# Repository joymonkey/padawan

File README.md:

# padawan
Padawan Pan-Galactic Sketch

Based on DanF's PADAWAN sketch for PS2 controllers, this sketch is intended to allow the use of PS2, PS3, PS4 or XBox 360 controllers depending on compile options set at the start of the sketch.

Tested with an Arduino Mega ADK, Padawan Shield, AZIO Class 1 Bluetooth USB Dongle, PS4 Controller, Heltec OLED, two WTV020SD-16P audio modules.

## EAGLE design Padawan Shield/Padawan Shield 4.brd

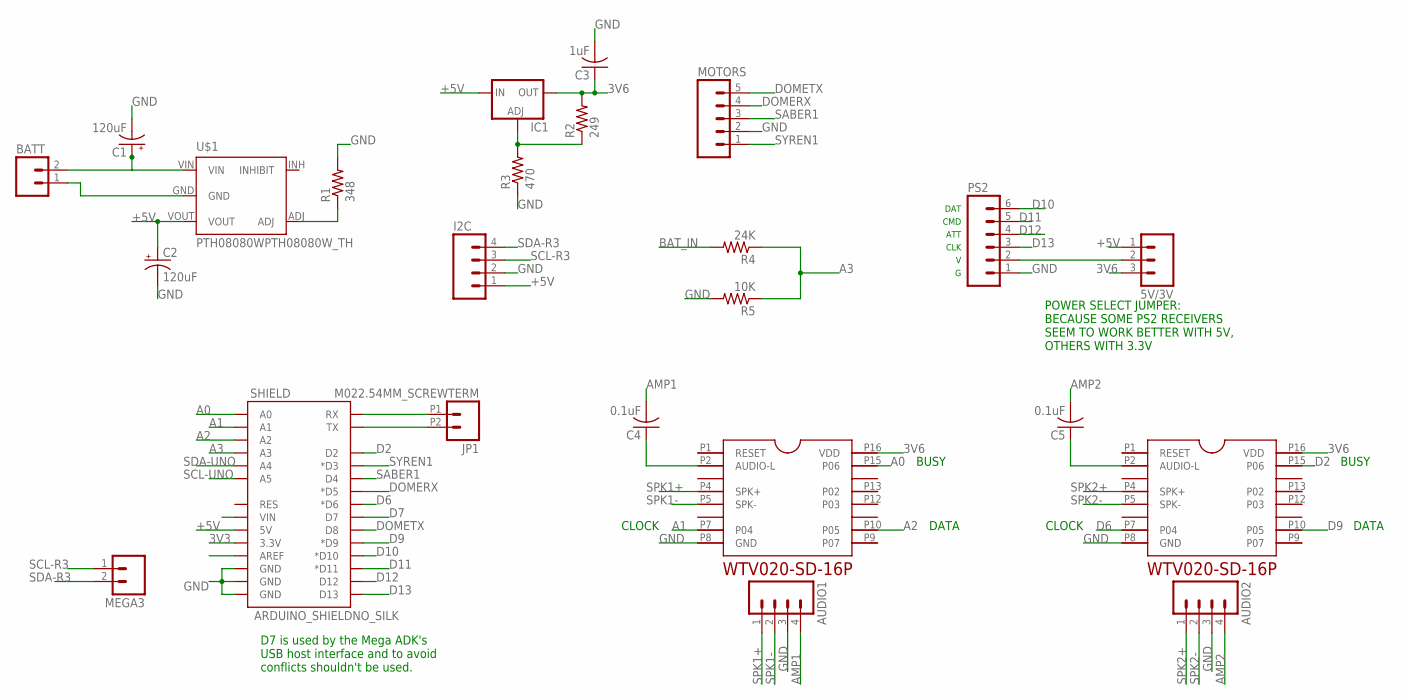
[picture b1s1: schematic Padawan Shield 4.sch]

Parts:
5V/3V: M03PTH; 1X03
AUDIO1, AUDIO2: M04PTH; 1X04
BATT: M02PTH; 1X02
C1, C2: 120uF; E2,5-6
C3: 1uF; C025-030X050
C4, C5: 0.1uF; C025-030X050
I2C: M04PTH; 1X04
IC1: LM317TS; 317TS
JP1: M022.54MM_SCREWTERM; 1X02_2.54_SCREWTERM
MEGA3: M021X02_NO_SILK; 1X02_NO_SILK
MOTORS: M05PTH; 1X05
PS2: M06SILK_FEMALE_PTH; 1X06
R1: 348; AXIAL-0.1EZ
R2: 249; AXIAL-0.1EZ
R3: 470; AXIAL-0.1EZ
R4: 24K; AXIAL-0.1EZ
R5: 10K; AXIAL-0.1EZ
SHIELD: ARDUINO_SHIELDNO_SILK; DUEMILANOVE_VIAS
U$1: PTH08080WPTH08080W_TH; PTH08080W_TH
WTV1, WTV2: WTV020-SD-16P; WTV020-16P

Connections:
3V3: SHIELD.3.3V
3V6: 5V/3V.3, C3.1, IC1.2 (OUT), R2.P$2 (2), WTV1.P16 (VDD), WTV2.P16 (VDD)
+5V: 5V/3V.1, C2.+, I2C.1, IC1.3 (IN), SHIELD.5V, U$1.VOUT
A0: SHIELD.A0, WTV1.P15 (P06)
A1: SHIELD.A1, WTV1.P7 (P04)
A2: SHIELD.A2, WTV1.P10 (P05)
A3: R4.P$1 (1), R5.P$1 (1), SHIELD.A3
AMP1: AUDIO1.4, C4.2
AMP2: AUDIO2.4, C5.2
BAT_IN: BATT.2, C1.+, R4.P$2 (2), U$1.VIN
D2: SHIELD.D2, WTV2.P15 (P06)
D6: SHIELD.D6 (*D6), WTV2.P7 (P04)
D7: SHIELD.D7
D9: SHIELD.D9 (*D9), WTV2.P10 (P05)
D10: PS2.6, SHIELD.D10 (*D10)
D11: PS2.5, SHIELD.D11 (*D11)
D12: PS2.4, SHIELD.D12
D13: PS2.3, SHIELD.D13
DOMERX: MOTORS.4, SHIELD.D5 (*D5)
DOMETX: MOTORS.5, SHIELD.D8
GND: AUDIO1.3, AUDIO2.3, BATT.1, C1.-, C2.-, C3.2, I2C.2, MOTORS.2, PS2.1, R1.P$2 (2), R3.P$1 (1), R5.P$2 (2), SHIELD.GND@0 (GND), SHIELD.GND@1 (GND), SHIELD.GND@2 (GND), U$1.GND, WTV1.P8 (GND), WTV2.P8 (GND)
unnamed: JP1.P1 (1), SHIELD.RX
unnamed: 5V/3V.2, PS2.2
unnamed: IC1.1 (ADJ), R2.P$1 (1), R3.P$2 (2)
unnamed: JP1.P2 (2), SHIELD.TX
unnamed: R1.P$1 (1), U$1.ADJ
unnamed: C4.1, WTV1.P2 (AUDIO-L)
unnamed: C5.1, WTV2.P2 (AUDIO-L)
SABER1: MOTORS.3, SHIELD.D4
SCL-R3: I2C.3, MEGA3.1
SCL-UNO: SHIELD.A5
SDA-R3: I2C.4, MEGA3.2
SDA-UNO: SHIELD.A4
SPK1+: AUDIO1.1, WTV1.P4 (SPK+)
SPK1-: AUDIO1.2, WTV1.P5 (SPK-)
SPK2+: AUDIO2.1, WTV2.P4 (SPK+)
SPK2-: AUDIO2.2, WTV2.P5 (SPK-)
SYREN1: MOTORS.1, SHIELD.D3 (*D3)

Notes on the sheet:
POWER SELECT JUMPER: BECAUSE SOME PS2 RECEIVERS SEEM TO WORK BETTER WITH 5V, OTHERS WITH 3.3V
D7 is used by the Mega ADK's USB host interface and to avoid conflicts shouldn't be used.
DAT CMD ATT CLK V G
BUSY
CLOCK
DATA

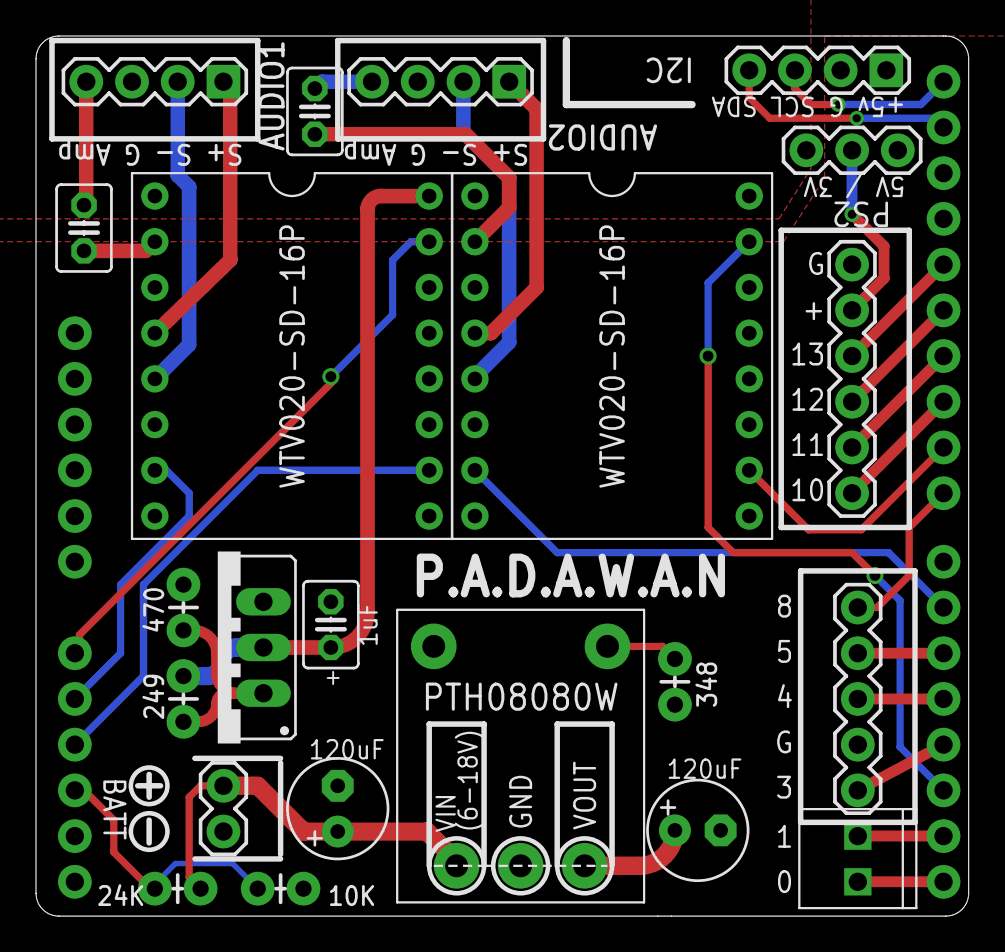
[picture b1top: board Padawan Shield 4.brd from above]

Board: 2 copper layers, 51.8 x 48.9 mm, 25 parts (1 on the bottom side), 34 nets.

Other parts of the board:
U$2: R2BUILDERS-LOGO

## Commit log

2015-03-23 Initial upload
2015-03-23 added Wtv library
2015-03-23 started copying over movement settings
2015-06-11 Added Padawan Arduino Shield files (Eagle format)

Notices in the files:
parts and their libraries:
SparkFun-Boards: Licensing: Creative Commons ShareAlike 4.0 International - https://creativecommons.org/licenses/by-sa/4.0
